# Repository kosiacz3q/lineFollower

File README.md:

# lineFollower

2015 LinerFollowers competion hosted by Posen University of Technology winner
https://www.youtube.com/watch?v=CigrI7Yh1Fk

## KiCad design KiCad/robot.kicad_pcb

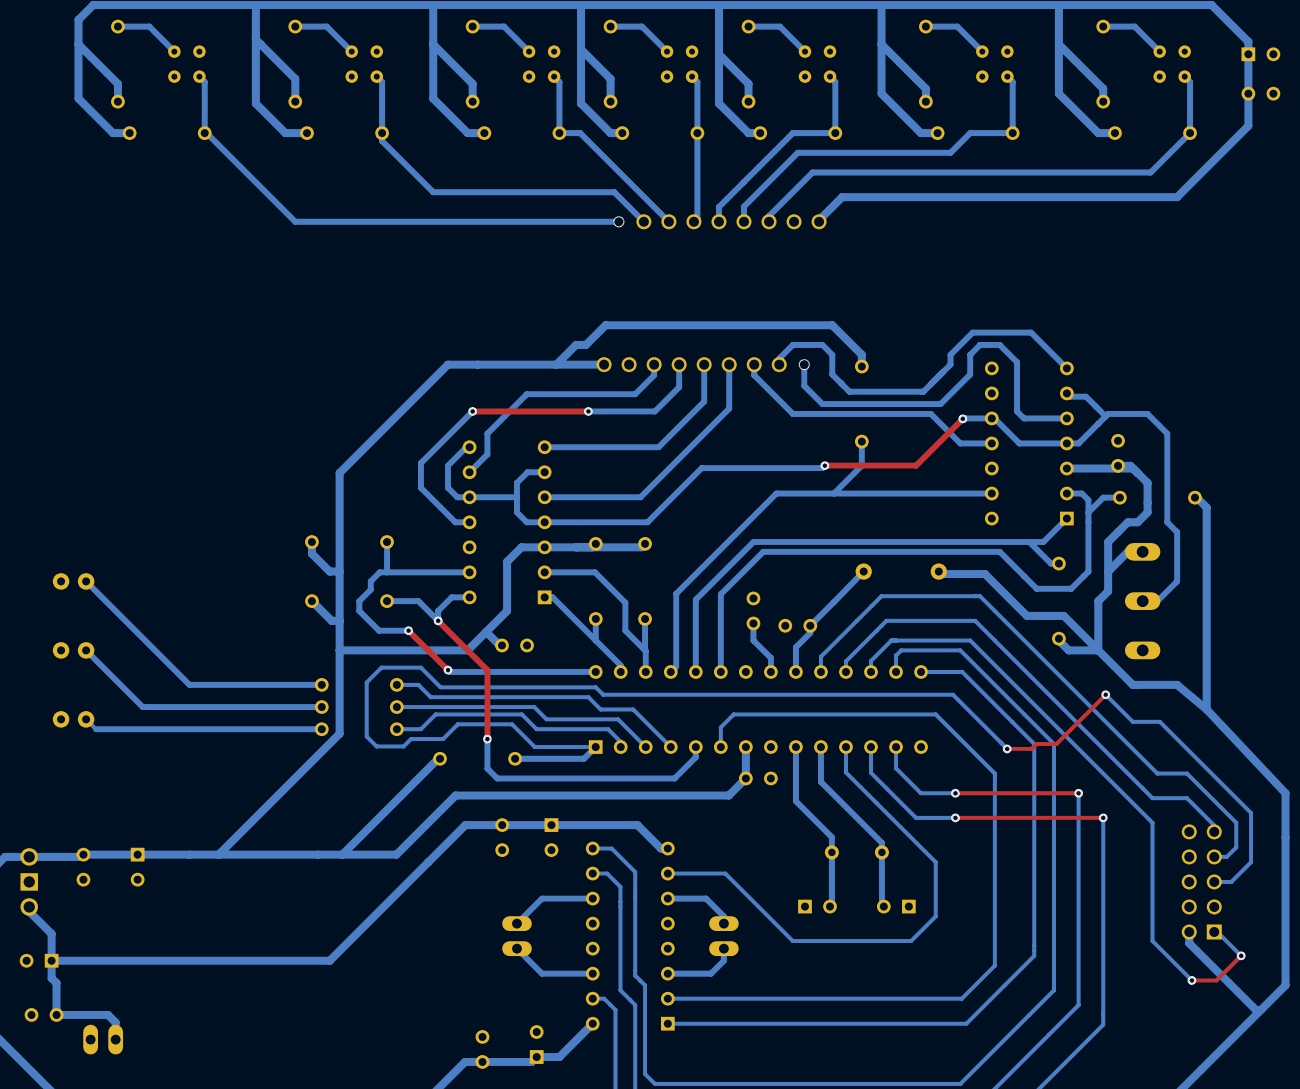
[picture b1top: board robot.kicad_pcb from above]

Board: 2 copper layers, 66 parts (0 on the bottom side), 57 nets.

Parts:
BT1: BATTERY; PINHEAD1-2
C1, C3, C5, C6, C7, C10, C13, C14, C17, C18: 100nF; C1
C2, C4: 47uF; C1V5
C8, C9: 22pF; C1V5
C11, C12: 10uF; C1V5
C15: 22uF; C1V5
D2, D3, D4: LED; LED-3MM
IC1: ATMEGA8A-P; DIP-28__300
IC2: L293D; DIP-16__300
L1: 10uH; R3-LARGE_PADS
P1: CONN_5X2; PIN_ARRAY_5x2
P2, P3: CONN_9; pinhead-1X09
P4, P5: CONN_2; PINHEAD1-2
R1, R9, R10, R11, R12, R13, R14, R15: 10k; R3
R3, R4, R5: 150; R3
R7: PC16S; piher-PC16S
R16, R17, R18, R19, R20, R21, R22: 240; R3
R41, R42, R43, R44, R45, R46, R47: 100k; R3
U1: 7805; LM78XXV
U4, U5, U6, U7, U8, U9, U10: CNY70; cny70-4
U20, U21: LM339; DIP-14__300
X1: CRYSTAL; HC-49V

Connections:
+5V: C3.1, C4.1, C5.1, C12.1, C13.1, C17.1, C18.2, IC1.7, IC2.16, L1.1, P1.2, P2.9, R1.1, R7.1E, R41.2, R42.2, R43.2, R44.2, R45.2, R46.2, R47.2, U1.VO, U20.3, U21.3
DIR_A1: IC1.6, IC2.2
DIR_A2: IC1.11, IC2.7
DIR_B1: IC1.12, IC2.15
DIR_B2: IC1.13, IC2.10
GND: BT1.2, C1.2, C2.2, C3.2, C4.2, C5.2, C6.2, C7.2, C8.1, C9.1, C10.1, C11.2, C12.2, C13.2, C14.1, C15.2, C17.2, C18.1, D2.2, D3.2, D4.2, IC1.8, IC1.22, IC2.4, IC2.5, IC2.12, IC2.13, P1.8, P1.10, P2.8, P3.8, R7.1A, U1.GND, U4.E, U4.K, U5.E, U5.K, U6.E, U6.K, U7.E, U7.K, U8.E, U8.K, U9.E, U9.K, U10.E, U10.K, U20.12, U21.12
K1: IC1.23, R41.1, U20.2
K2: IC1.24, R42.1, U20.1
K3: IC1.25, R43.1, U20.13
K4: IC1.26, R44.1, U21.2
K5: IC1.27, R45.1, U21.1
K6: IC1.28, R46.1, U21.13
K7: IC1.5, R47.1, U21.14
MISO: IC1.18, P1.9
MOSI: IC1.17, P1.1
unnamed: P3.5, R13.2, U8.C
unnamed: P3.4, R12.2, U7.C
unnamed: P3.7, R15.2, U10.C
unnamed: P3.6, R14.2, U9.C
unnamed: IC1.2, R3.1
unnamed: IC1.3, R4.1
unnamed: D2.1, R3.2
unnamed: D3.1, R4.2
unnamed: D4.1, R5.2
unnamed: R17.1, U5.A
unnamed: R18.1, U6.A
unnamed: R19.1, U7.A
unnamed: R20.1, U8.A
unnamed: R21.1, U9.A
unnamed: R22.1, U10.A
unnamed: R16.1, U4.A
unnamed: IC2.6, P4.1
unnamed: IC2.3, P4.2
unnamed: IC2.11, P5.2
unnamed: C9.2, IC1.10, X1.1
unnamed: C8.2, IC1.9, X1.2
unnamed: IC2.14, P5.1
unnamed: C7.1, IC1.21
unnamed: IC1.4, R5.1
unnamed: C6.1, IC1.20, L1.2
unnamed: P2.3, U20.11
unnamed: P2.7, U21.9
unnamed: P2.6, U21.11
unnamed: P2.5, U21.7
unnamed: P2.4, U21.5
unnamed: P2.2, U20.7
unnamed: P2.1, U20.5
unnamed: R7.1S, U20.4, U20.6, U20.10, U21.4, U21.6, U21.8, U21.10
unnamed: P3.1, R9.2, U4.C
unnamed: P3.3, R11.2, U6.C
unnamed: P3.2, R10.2, U5.C
PWM_A: IC1.15, IC2.1
PWM_B: IC1.16, IC2.9
RST: IC1.1, P1.5, R1.2
SCK: IC1.19, P1.7
VCC: BT1.1, C1.1, C2.1, C14.2, C15.1, IC2.8, U1.VI
V_CNY: C10.2, C11.1, P3.9, R9.1, R10.1, R11.1, R12.1, R13.1, R14.1, R15.1, R16.2, R17.2, R18.2, R19.2, R20.2, R21.2, R22.2

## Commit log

2015-05-05 program
2015-05-05 projekt płytki
2015-05-05 fotki_filmy
2015-05-05 Fotki
2015-05-05 fotki fotki fotki
2015-05-05 Filmik z wiercenia
2015-05-06 FilmikiMetodaTermoTransferowa
    jw.
2015-05-10 lk pwm test 2
2015-05-11 simple engine control
2015-05-11 pwm engine test 2
2015-05-11 pwm engine test 3
2015-05-11 nowe fotki
2015-05-12 first pid version
2015-05-13 PID working
2015-05-14 Pawlok lapaj
2015-05-14 Some changes to PWM
2015-05-14 zmiany
2015-05-14 coś tam działa
2015-05-14 Projects merged
2015-05-16 Round removed code formatting
2015-05-17 avr gitignore
2015-05-17 value indicator
2015-05-17 compilable
2015-05-17 Major changes Project added, Regions added, new sensor reading
2015-05-17 new ignores added
2015-05-17 New PID
2015-05-18 Poprawka?
2015-05-20 minor changes
2015-05-21 integral part fixed minor fixes
2015-05-21 Cofanie działa ale nie działa robot.
2015-05-21 Revert "v1"
    This reverts commit de57f09d34648b62c9088b67d935d9ee4f964cea.
2015-05-21 minor fixes
2015-05-21 old pid restored
2015-05-21 Piezol nie wie co chce
2015-05-21 Working PID with brakes jp2gmd
2015-05-21 pid working pretty well
2015-05-22 ultimate winner PID
2015-05-27 code cleaned
2015-05-27 version for dtr v1.0
